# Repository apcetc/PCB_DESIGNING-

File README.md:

# PCB_DESIGNING-
## list of project
1. https://github.com/apcetc/PCB_DESIGNING-/blob/main/FIRST_DEV_BORAD/read.md

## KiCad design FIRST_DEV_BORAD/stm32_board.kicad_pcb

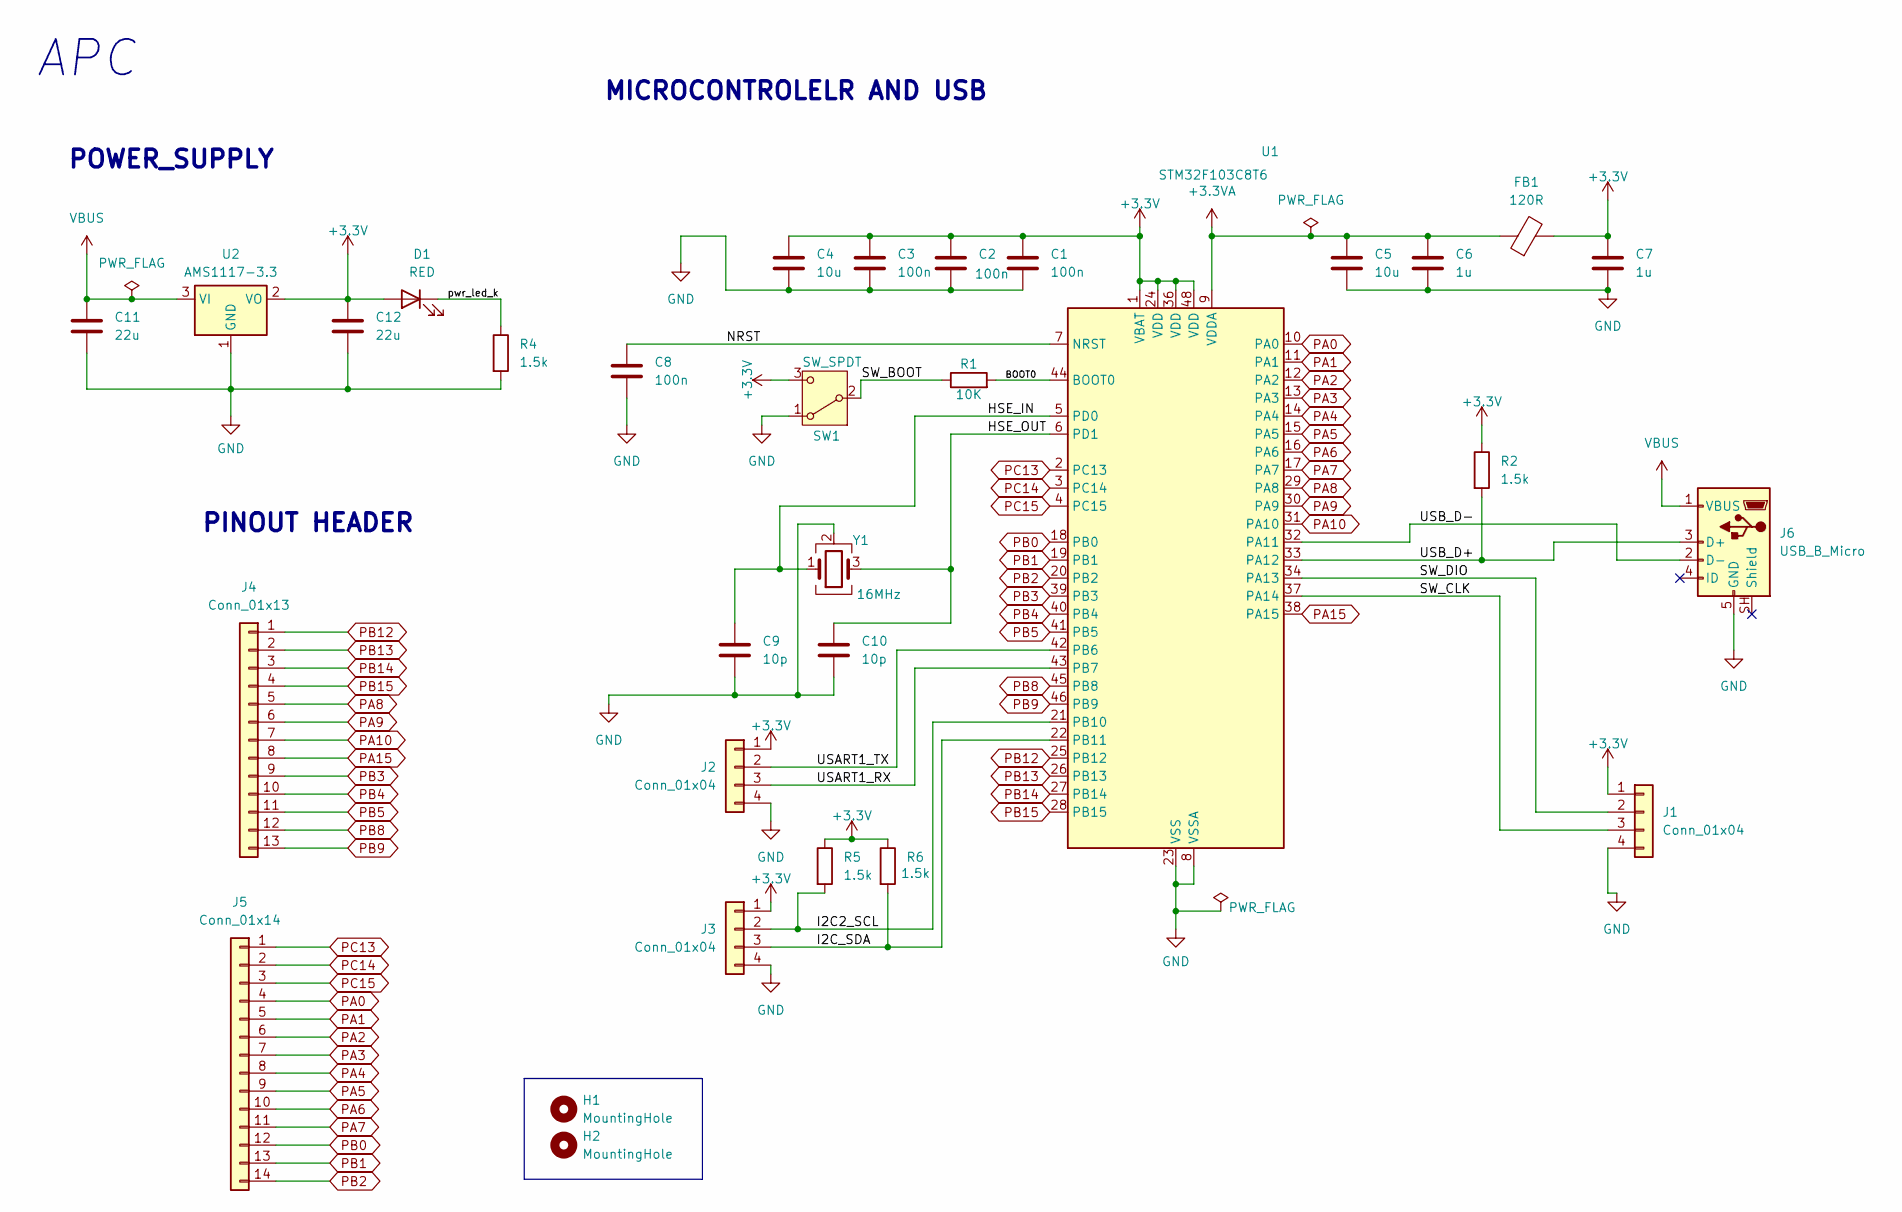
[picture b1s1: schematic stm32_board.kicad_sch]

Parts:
C1, C2, C3, C8: 100n; C_0805_2012Metric
C4, C5: 10u; C_0805_2012Metric
C6, C7: 1u; C_0805_2012Metric
C9, C10: 10p; C_0805_2012Metric
C11, C12: 22u; C_0805_2012Metric
D1: RED; LED_0603_1608Metric
FB1: 120R; L_0603_1608Metric
H1, H2: MountingHole; MountingHole_3.2mm_M3
J1, J2, J3: Conn_01x04; PinHeader_1x04_P2.54mm_Vertical
J4: Conn_01x13; PinHeader_1x13_P2.54mm_Vertical
J5: Conn_01x14; PinHeader_1x14_P2.54mm_Vertical
J6: USB_B_Micro; USB_Mini-B_Lumberg_2486_01_Horizontal
R1: 10K; R_0805_2012Metric
R2, R4, R5, R6: 1.5k; R_0805_2012Metric
SW1: SW_SPDT; SW_Slide_SPDT_Straight_CK_OS102011MS2Q
U1: STM32F103C8T6; LQFP-48_7x7mm_P0.5mm
U2: AMS1117-3.3; SOT-223-3_TabPin2
Y1: 16MHz; Crystal_SMD_3225-4Pin_3.2x2.5mm

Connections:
+3.3V: C1.1, C2.1, C3.1, C4.1, C7.1, C12.1, D1.2 (A), FB1.2, J1.1, J2.1, J3.1, R2.1, R5.1, R6.1, SW1.3 (C), U1.1 (VBAT), U1.24 (VDD), U1.36 (VDD), U1.48 (VDD), U2.2 (VO)
+3.3VA: C5.1, C6.1, FB1.1, U1.9 (VDDA)
/BOOT0: R1.2, U1.44 (BOOT0)
/HSE_IN: C9.1, U1.5 (PD0), Y1.1
/HSE_OUT: C10.1, U1.6 (PD1), Y1.3
/I2C2_SCL: J3.2, R5.2, U1.21 (PB10)
/I2C_SDA: J3.3, R6.2, U1.22 (PB11)
/NRST: C8.1, U1.7 (NRST)
/SW_BOOT: R1.1, SW1.2 (B)
/SW_CLK: J1.3, U1.37 (PA14)
/SW_DIO: J1.2, U1.34 (PA13)
/USART1_RX: J2.3, U1.43 (PB7)
/USART1_TX: J2.2, U1.42 (PB6)
/USB_D+: J6.3 (D+), R2.2, U1.33 (PA12)
/USB_D-: J6.2 (D-), U1.32 (PA11)
/pwr_led_k: D1.1 (K), R4.1
GND: C1.2, C2.2, C3.2, C4.2, C5.2, C6.2, C7.2, C8.2, C9.2, C10.2, C11.2, C12.2, J1.4, J2.4, J3.4, J6.5 (GND), R4.2, SW1.1 (A), U1.8 (VSSA), U1.23 (VSS), U1.35 (VSS), U1.47 (VSS), U2.1 (GND), Y1.2 (G), Y1.4 (G)
PA0: J5.4, U1.10 (PA0)
PA1: J5.5, U1.11 (PA1)
PA2: J5.6, U1.12 (PA2)
PA3: J5.7, U1.13 (PA3)
PA4: J5.8, U1.14 (PA4)
PA5: J5.9, U1.15 (PA5)
PA6: J5.10, U1.16 (PA6)
PA7: J5.11, U1.17 (PA7)
PA8: J4.5, U1.29 (PA8)
PA9: J4.6, U1.30 (PA9)
PA10: J4.7, U1.31 (PA10)
PA15: J4.8, U1.38 (PA15)
PB0: J5.12, U1.18 (PB0)
PB1: J5.13, U1.19 (PB1)
PB2: J5.14, U1.20 (PB2)
PB3: J4.9, U1.39 (PB3)
PB4: J4.10, U1.40 (PB4)
PB5: J4.11, U1.41 (PB5)
PB8: J4.12, U1.45 (PB8)
PB9: J4.13, U1.46 (PB9)
PB12: J4.1, U1.25 (PB12)
PB13: J4.2, U1.26 (PB13)
PB14: J4.3, U1.27 (PB14)
PB15: J4.4, U1.28 (PB15)
PC13: J5.1, U1.2 (PC13)
PC14: J5.2, U1.3 (PC14)
PC15: J5.3, U1.4 (PC15)
VBUS: C11.1, J6.1 (VBUS), U2.3 (VI)

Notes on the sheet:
POWER_SUPPLY
PINOUT HEADER
APC
MICROCONTROLELR AND USB

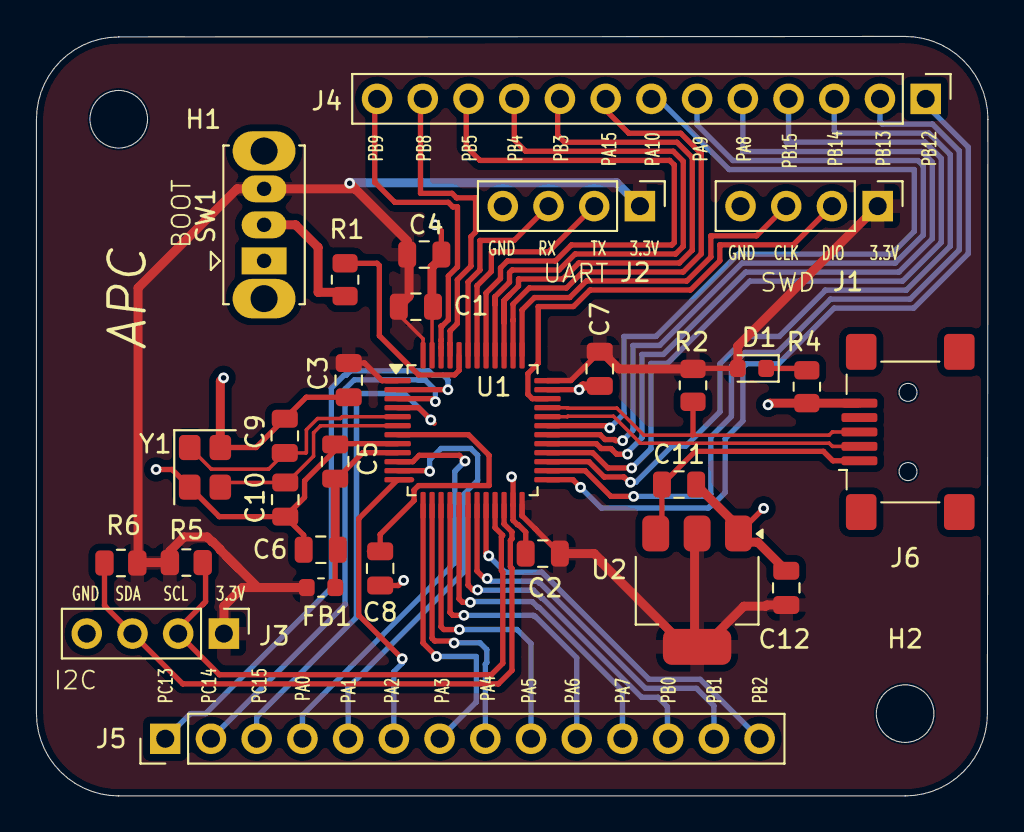
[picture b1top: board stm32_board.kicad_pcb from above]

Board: 2 copper layers, 52.9 x 42.2 mm, 31 parts (0 on the bottom side), 45 nets.
